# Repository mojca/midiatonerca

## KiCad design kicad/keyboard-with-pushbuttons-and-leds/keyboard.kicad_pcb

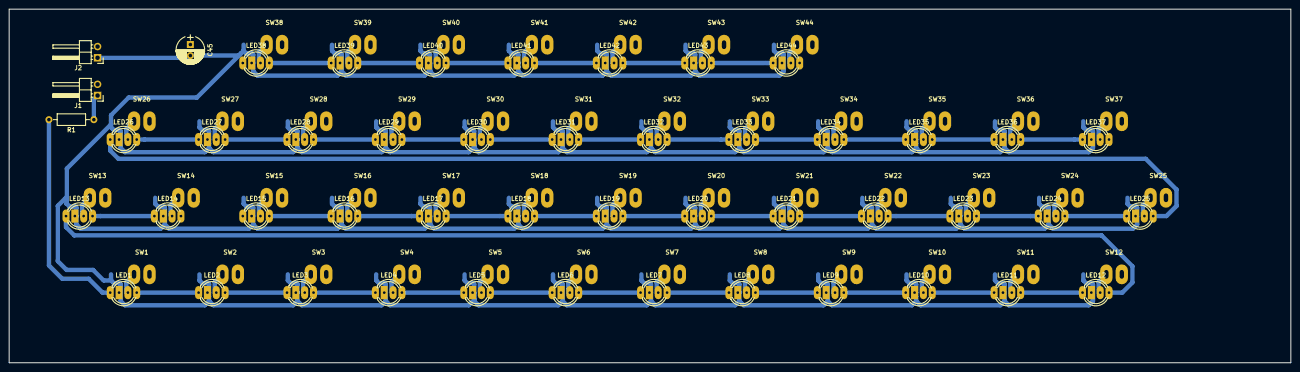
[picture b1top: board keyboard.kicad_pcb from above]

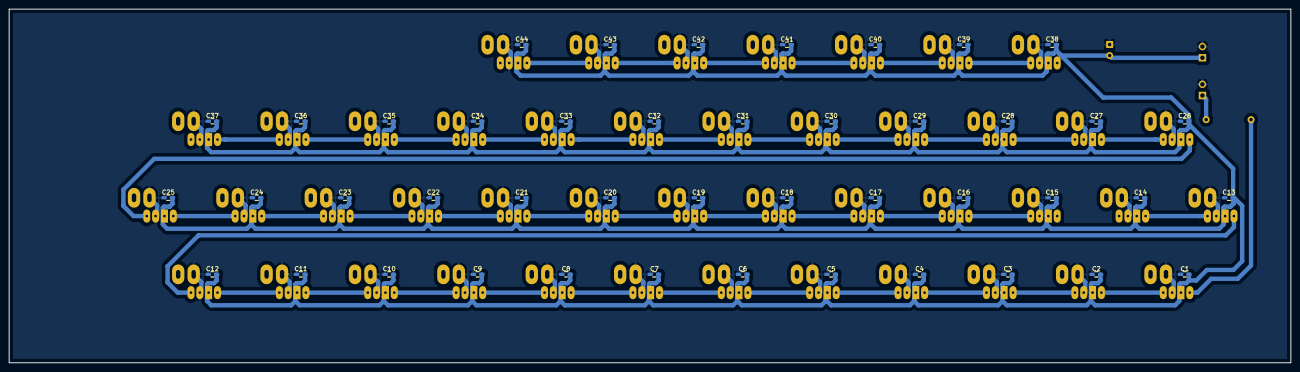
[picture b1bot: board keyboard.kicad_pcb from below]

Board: 2 copper layers, 290.0 x 80.0 mm, 136 parts (44 on the bottom side), 47 nets.

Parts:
C1, C2, C3, C4, C5, C6, C7, C8, C9, C10, C11, C12, C13, C14, C15, C16, C17, C18, C19, C20, C21, C22, C23, C24, C25, C26, C27, C28, C29, C30, C31, C32, C33, C34, C35, C36, C37, C38, C39, C40, C41, C42, C43, C44: C; C_0603_HandSoldering
C45: 1000uF; CP_Radial_D6.3mm_P2.50mm
J1, J2: CONN_01X02_MALE; Pin_Header_Angled_1x02_Pitch2.54mm
LED1, LED2, LED3, LED4, LED5, LED6, LED7, LED8, LED9, LED10, LED11, LED12, LED13, LED14, LED15, LED16, LED17, LED18, LED19, LED20, LED21, LED22, LED23, LED24, LED25, LED26, LED27, LED28, LED29, LED30, LED31, LED32, LED33, LED34, LED35, LED36, LED37, LED38, LED39, LED40, LED41, LED42, LED43, LED44: WS2812B; LED_D5.0mm-4-2mm
R1: 270R; R_Axial_DIN0207_L6.3mm_D2.5mm_P10.16mm_Horizontal
SW1, SW2, SW3, SW4, SW5, SW6, SW7, SW8, SW9, SW10, SW11, SW12, SW13, SW14, SW15, SW16, SW17, SW18, SW19, SW20, SW21, SW22, SW23, SW24, SW25, SW26, SW27, SW28, SW29, SW30, SW31, SW32, SW33, SW34, SW35, SW36, SW37, SW38, SW39, SW40, SW41, SW42, SW43, SW44: SW_Push; SW_PUSH_6mm

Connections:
GND: C1.1, C2.1, C3.1, C4.1, C5.1, C6.1, C7.1, C8.1, C9.1, C10.1, C11.1, C12.1, C13.1, C14.1, C15.1, C16.1, C17.1, C18.1, C19.1, C20.1, C21.1, C22.1, C23.1, C24.1, C25.1, C26.1, C27.1, C28.1, C29.1, C30.1, C31.1, C32.1, C33.1, C34.1, C35.1, C36.1, C37.1, C38.1, C39.1, C40.1, C41.1, C42.1, C43.1, C44.1, C45.1, J1.2, J2.2, LED1.3, LED2.3, LED3.3, LED4.3, LED5.3, LED6.3, LED7.3, LED8.3, LED9.3, LED10.3, LED11.3, LED12.3, LED13.3, LED14.3, LED15.3, LED16.3, LED17.3, LED18.3, LED19.3, LED20.3, LED21.3, LED22.3, LED23.3, LED24.3, LED25.3, LED26.3, LED27.3, LED28.3, LED29.3, LED30.3, LED31.3, LED32.3, LED33.3, LED34.3, LED35.3, LED36.3, LED37.3, LED38.3, LED39.3, LED40.3, LED41.3, LED42.3, LED43.3, LED44.3, SW1.1, SW2.1, SW3.1, SW4.1, SW5.1, SW6.1, SW7.1, SW8.1, SW9.1, SW10.1, SW11.1, SW12.1, SW13.1, SW14.1, SW15.1, SW16.1, SW17.1, SW18.1, SW19.1, SW20.1, SW21.1, SW22.1, SW23.1, SW24.1, SW25.1, SW26.1, SW27.1, SW28.1, SW29.1, SW30.1, SW31.1, SW32.1, SW33.1, SW34.1, SW35.1, SW36.1, SW37.1, SW38.1, SW39.1, SW40.1, SW41.1, SW42.1, SW43.1, SW44.1
unnamed: J1.1, R1.1
unnamed: LED1.2, LED2.4
unnamed: LED1.4, R1.2
unnamed: LED2.2, LED3.4
unnamed: LED3.2, LED4.4
unnamed: LED4.2, LED5.4
unnamed: LED5.2, LED6.4
unnamed: LED6.2, LED7.4
unnamed: LED7.2, LED8.4
unnamed: LED8.2, LED9.4
unnamed: LED10.2, LED11.4
unnamed: LED9.2, LED10.4
unnamed: LED11.2, LED12.4
unnamed: LED12.2, LED13.4
unnamed: LED13.2, LED14.4
unnamed: LED14.2, LED15.4
unnamed: LED15.2, LED16.4
unnamed: LED16.2, LED17.4
unnamed: LED17.2, LED18.4
unnamed: LED18.2, LED19.4
unnamed: LED19.2, LED20.4
unnamed: LED20.2, LED21.4
unnamed: LED21.2, LED22.4
unnamed: LED22.2, LED23.4
unnamed: LED23.2, LED24.4
unnamed: LED24.2, LED25.4
unnamed: LED25.2, LED26.4
unnamed: LED26.2, LED27.4
unnamed: LED27.2, LED28.4
unnamed: LED28.2, LED29.4
unnamed: LED29.2, LED30.4
unnamed: LED30.2, LED31.4
unnamed: LED31.2, LED32.4
unnamed: LED32.2, LED33.4
unnamed: LED33.2, LED34.4
unnamed: LED34.2, LED35.4
unnamed: LED35.2, LED36.4
unnamed: LED36.2, LED37.4
unnamed: LED37.2, LED38.4
unnamed: LED38.2, LED39.4
unnamed: LED39.2, LED40.4
unnamed: LED40.2, LED41.4
unnamed: LED41.2, LED42.4
unnamed: LED42.2, LED43.4
unnamed: LED43.2, LED44.4
VccLed: C1.2, C2.2, C3.2, C4.2, C5.2, C6.2, C7.2, C8.2, C9.2, C10.2, C11.2, C12.2, C13.2, C14.2, C15.2, C16.2, C17.2, C18.2, C19.2, C20.2, C21.2, C22.2, C23.2, C24.2, C25.2, C26.2, C27.2, C28.2, C29.2, C30.2, C31.2, C32.2, C33.2, C34.2, C35.2, C36.2, C37.2, C38.2, C39.2, C40.2, C41.2, C42.2, C43.2, C44.2, C45.2, J2.1, LED1.1, LED2.1, LED3.1, LED4.1, LED5.1, LED6.1, LED7.1, LED8.1, LED9.1, LED10.1, LED11.1, LED12.1, LED13.1, LED14.1, LED15.1, LED16.1, LED17.1, LED18.1, LED19.1, LED20.1, LED21.1, LED22.1, LED23.1, LED24.1, LED25.1, LED26.1, LED27.1, LED28.1, LED29.1, LED30.1, LED31.1, LED32.1, LED33.1, LED34.1, LED35.1, LED36.1, LED37.1, LED38.1, LED39.1, LED40.1, LED41.1, LED42.1, LED43.1, LED44.1
